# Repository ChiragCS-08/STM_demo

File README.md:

# STM_demo
This is an STM demo pcb Design with USB-C and LDO power supply utilizing a PI Network to filter noise.

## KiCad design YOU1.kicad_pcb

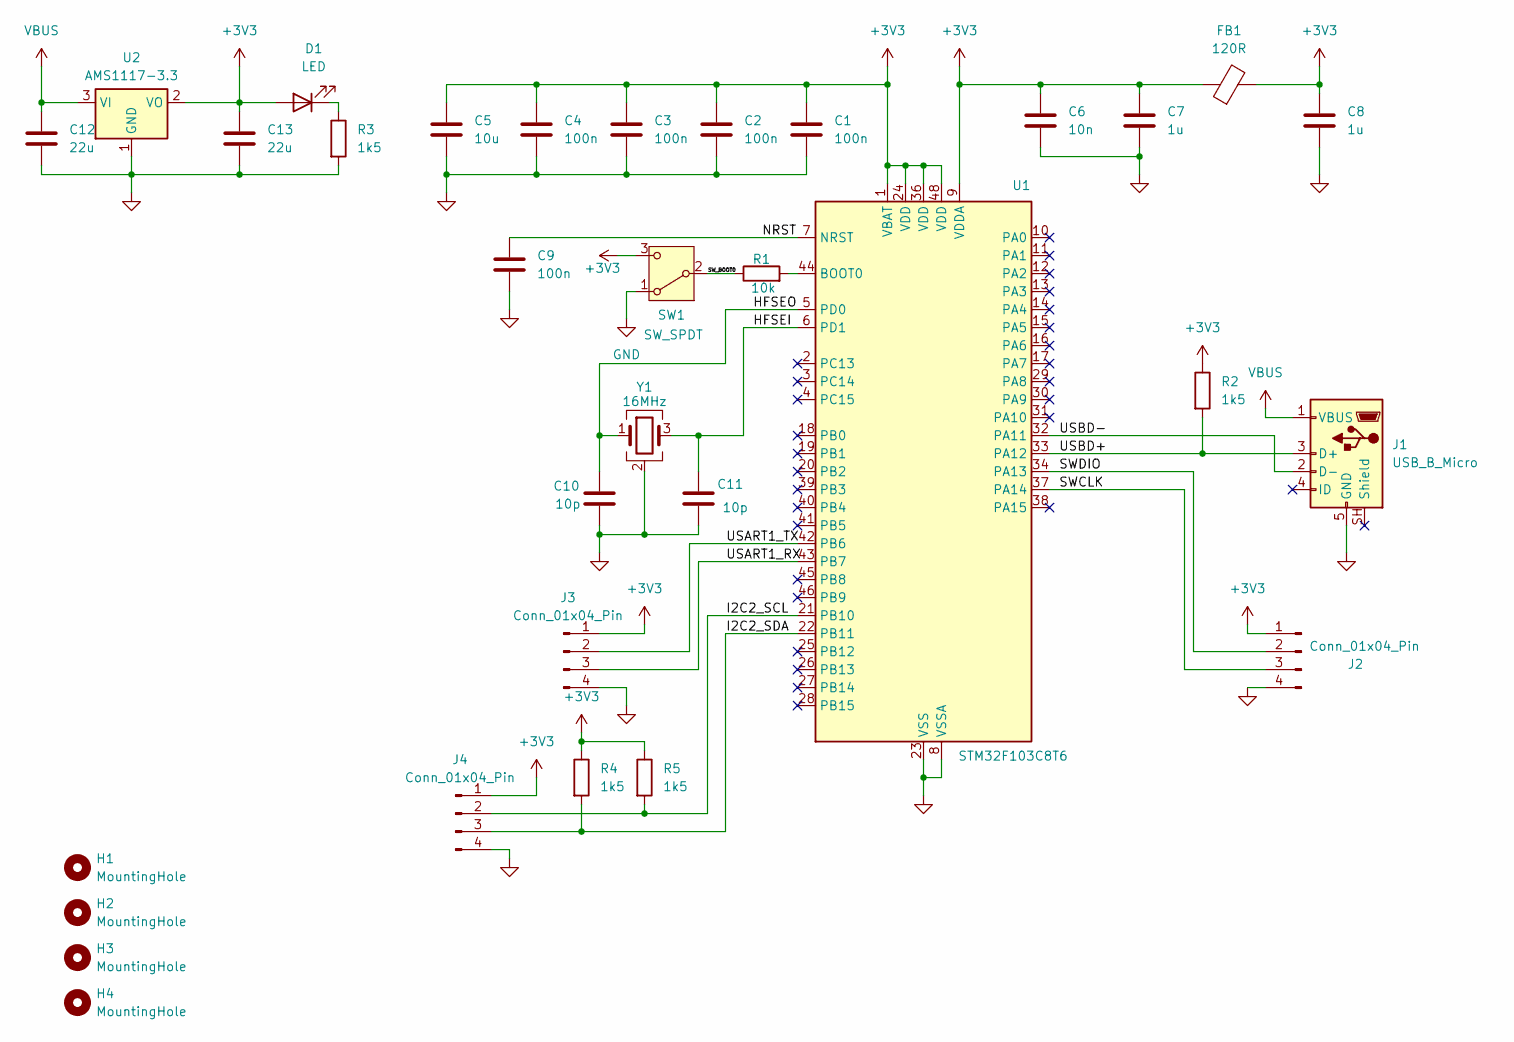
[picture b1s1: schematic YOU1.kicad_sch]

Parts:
C1, C2, C3, C4: 100n; C_0603_1608Metric_Pad1.08x0.95mm_HandSolder
C5: 10u; C_0603_1608Metric_Pad1.08x0.95mm_HandSolder
C6: 10n; C_0603_1608Metric_Pad1.08x0.95mm_HandSolder
C7, C8: 1u; C_0603_1608Metric_Pad1.08x0.95mm_HandSolder
C9: 100n; C_0504_1310Metric
C10, C11: 10p; C_0504_1310Metric
C12, C13: 22u; C_0603_1608Metric_Pad1.08x0.95mm_HandSolder
D1: LED; LED_0805_2012Metric
FB1: 120R; L_Eaton_MCL2012V1
H1, H2, H3, H4: MountingHole; MountingHole_2.2mm_M2_ISO14580_Pad
J1: USB_B_Micro; USB_Micro-B_Amphenol_10118193-0001LF_Horizontal
J2, J3, J4: Conn_01x04_Pin; PinHeader_1x04_P1.00mm_Vertical
R1: 10k; R_0201_0603Metric_Pad0.64x0.40mm_HandSolder
R2, R3, R4, R5: 1k5; R_0805_2012Metric
SW1: SW_SPDT; SW_SPDT_PCM12
U1: STM32F103C8T6; LQFP-48_7x7mm_P0.5mm
U2: AMS1117-3.3; SOT-223-3_TabPin2
Y1: 16MHz; Oscillator_SMD_SeikoEpson_SG3030CM

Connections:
+3V3: C1.1, C2.1, C3.1, C4.1, C5.1, C6.1, C7.1, C8.1, C13.1, D1.2 (A), FB1.1, FB1.2, J2.1, J3.1, J4.1, R2.1, R4.1, R5.1, SW1.3 (C), U1.1 (VBAT), U1.9 (VDDA), U1.24 (VDD), U1.36 (VDD), U1.48 (VDD), U2.2 (VO)
/HFSEI: C11.1, U1.6 (PD1), Y1.3
/HFSEO: C10.1, U1.5 (PD0), Y1.1
/I2C2_SCL: J4.2, R5.2, U1.21 (PB10)
/I2C2_SDA: J4.3, R4.2, U1.22 (PB11)
/NRST: C9.1, U1.7 (NRST)
/SWCLK: J2.3, U1.37 (PA14)
/SWDIO: J2.2, U1.34 (PA13)
/SW_BOOT0: R1.1, SW1.2 (B)
/USART1_RX: J3.3, U1.43 (PB7)
/USART1_TX: J3.2, U1.42 (PB6)
/USBD+: J1.3 (D+), R2.2, U1.33 (PA12)
/USBD-: J1.2 (D-), U1.32 (PA11)
GND: C1.2, C2.2, C3.2, C4.2, C5.2, C6.2, C7.2, C8.2, C9.2, C10.2, C11.2, C12.2, C13.2, J1.5 (GND), J2.4, J3.4, J4.4, R3.2, SW1.1 (A), U1.8 (VSSA), U1.23 (VSS), U1.35 (VSS), U1.47 (VSS), U2.1 (GND), Y1.2 (G), Y1.4 (G)
unnamed: D1.1 (K), R3.1
unnamed: R1.2, U1.44 (BOOT0)
VBUS: C12.1, J1.1 (VBUS), U2.3 (VI)

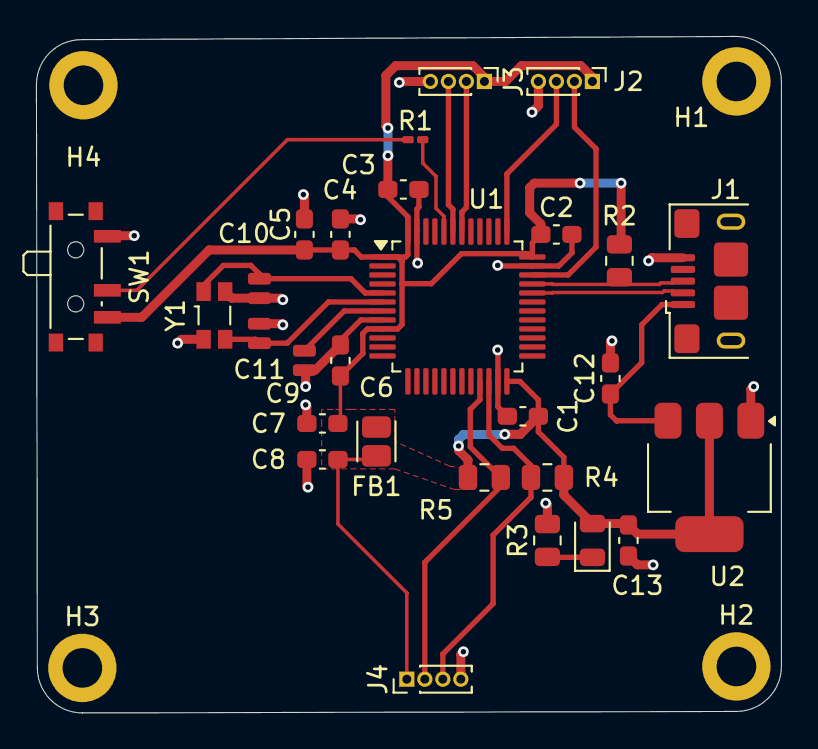
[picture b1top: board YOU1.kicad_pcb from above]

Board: 2 copper layers, 41.4 x 37.6 mm, 32 parts (0 on the bottom side), 17 nets.
